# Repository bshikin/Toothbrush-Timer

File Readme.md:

Toothbrush Timer
=================

This is a repository for my toothbrush timer project. It contains schematic and enclosure design and program sources.

You can read how the timer was made in [this Instructable](http://instructables.com/id/Toothbrush-Timer)

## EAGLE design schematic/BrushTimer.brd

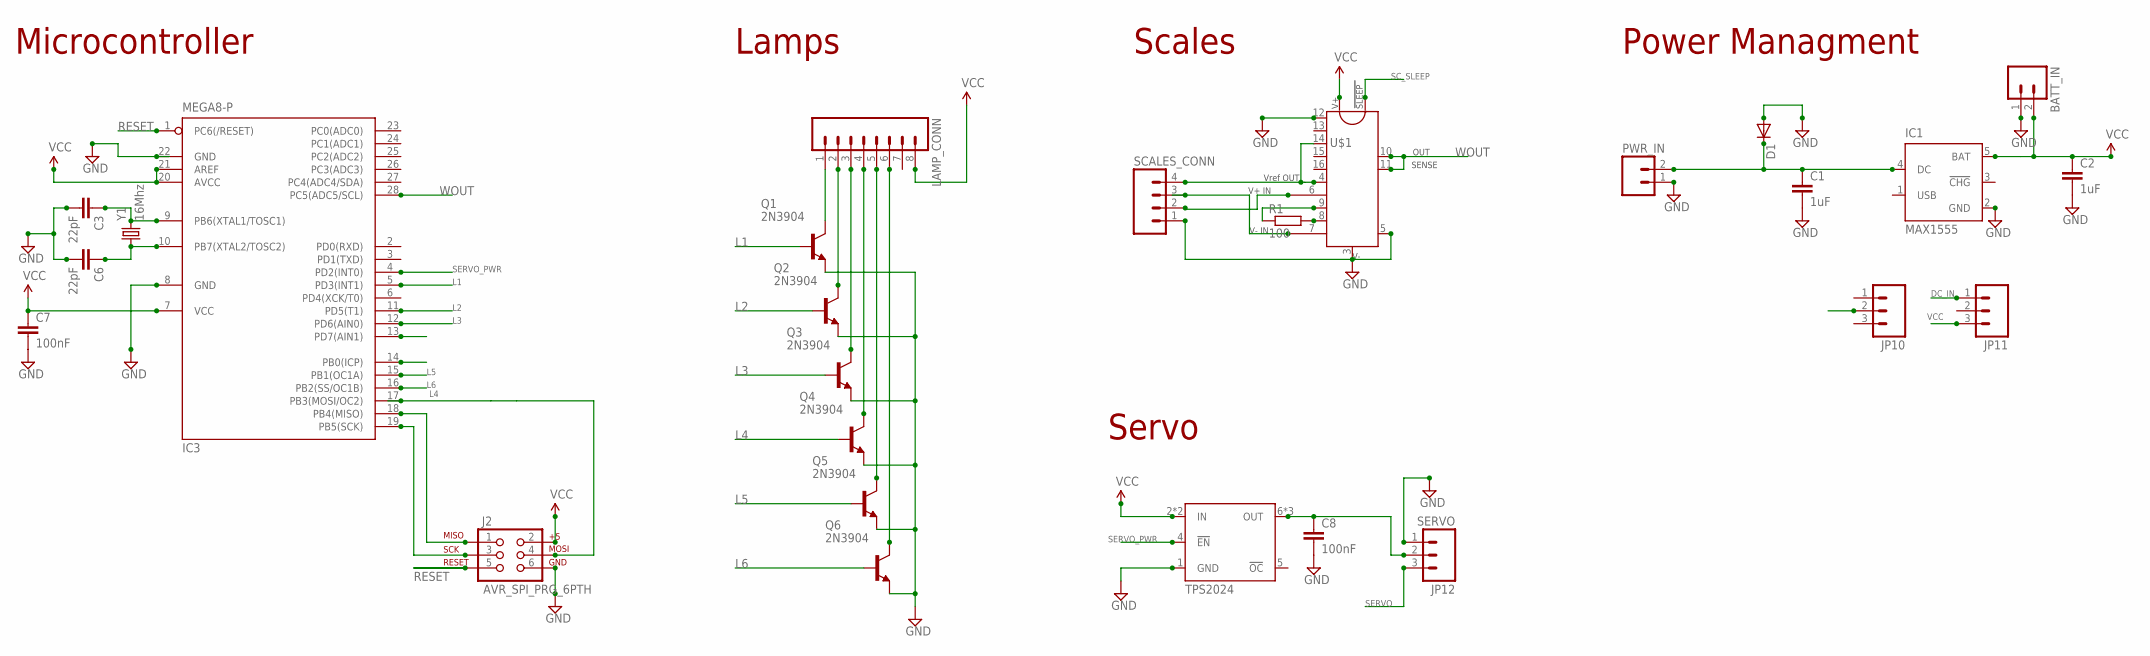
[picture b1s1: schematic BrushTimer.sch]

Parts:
BATT_IN: M02PTH; 1X02
C1, C2: 1uF; AXIAL-5MM
C3, C6: 22pF; C2.5-2
C7, C8: 100nF; C5B3.5
D1: DIODE-D-2.5; D-2.5
IC1: MAX1555; SOT23-5L
IC3: MEGA8-P; DIL28-3
J2: AVR_SPI_PRG_6PTH; 2X3
JP10, JP11: M03PTH; 1X03
JP12: SERVO; 1X03
LAMP_CONN: M081X08; 1X08
PWR_IN: M02PTH; 1X02
Q1, Q2, Q3, Q4, Q5, Q6: 2N3904; TO92
R1: 100; 0207/5V
SCALES_CONN: M04PTH; 1X04
U$1: INA125; DIL16
U$2: TPS2024; DIL08-OPTO
Y1: 16Mhz; HC49US

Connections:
DC_IN: C1.P$1 (1), D1.C, IC1.4 (DC), JP11.1, PWR_IN.2
GND: BATT_IN.1, C1.P$2 (2), C2.P$2 (2), C3.2, C6.2, C7.2, C8.2, D1.A, IC1.2 (GND), IC3.8 (GND), IC3.22 (GND), J2.6, JP10.2, JP12.1, PWR_IN.1, Q1.3 (E), Q2.3 (E), Q3.3 (E), Q4.3 (E), Q5.3 (E), Q6.3 (E), SCALES_CONN.1, U$1.3, U$1.5, U$1.12, U$2.1 (GND)
L1: IC3.5 (PD3(INT1)), Q1.2 (B)
L1_OUT: LAMP_CONN.1, Q1.1 (C)
L2: IC3.11 (PD5(T1)), Q2.2 (B)
L2_OUT: LAMP_CONN.2, Q2.1 (C)
L3: IC3.12 (PD6(AIN0)), Q3.2 (B)
L3_OUT: LAMP_CONN.3, Q3.1 (C)
L4: IC3.17 (PB3(MOSI/OC2)), J2.4, Q4.2 (B)
L4_OUT: LAMP_CONN.4, Q4.1 (C)
L5: IC3.15 (PB1(OC1A)), Q5.2 (B)
L5_OUT: LAMP_CONN.5, Q5.1 (C)
L6: IC3.16 (PB2(SS/OC1B)), Q6.2 (B)
L6_OUT: LAMP_CONN.6, Q6.1 (C)
MISO: IC3.18 (PB4(MISO)), J2.1
unnamed: SCALES_CONN.2, U$1.6
RESET: IC3.1 (PC6(/RESET)), J2.5
RG1: R1.1, U$1.9
RG2: R1.2, U$1.8
SCK: IC3.19 (PB5(SCK)), J2.3
SC_SLEEP: IC3.13 (PD7(AIN1)), U$1.2
SERVO: IC3.14 (PB0(ICP)), JP12.3
SERVO_PWR: IC3.4 (PD2(INT0)), U$2.4 (!EN)
SERVO_VCC: C8.1, JP12.2, U$2.6 (OUT), U$2.7 (OUT), U$2.8 (OUT)
V-IN: SCALES_CONN.3, U$1.7
VCC: BATT_IN.2, C2.P$1 (1), C7.1, IC1.5 (BAT), IC3.7 (VCC), IC3.20 (AVCC), IC3.21 (AREF), J2.2, JP11.3, LAMP_CONN.8, U$1.1, U$2.2 (IN), U$2.3 (IN)
VREF-OUT: SCALES_CONN.4, U$1.4, U$1.14
WOUT: IC3.28 (PC5(ADC5/SCL)), U$1.10, U$1.11
XTAL9: C3.1, IC3.9 (PB6(XTAL1/TOSC1)), Y1.2
XTAL19: C6.1, IC3.10 (PB7(XTAL2/TOSC2)), Y1.1

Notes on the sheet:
Microcontroller
Lamps
Scales
Power Managment
Servo

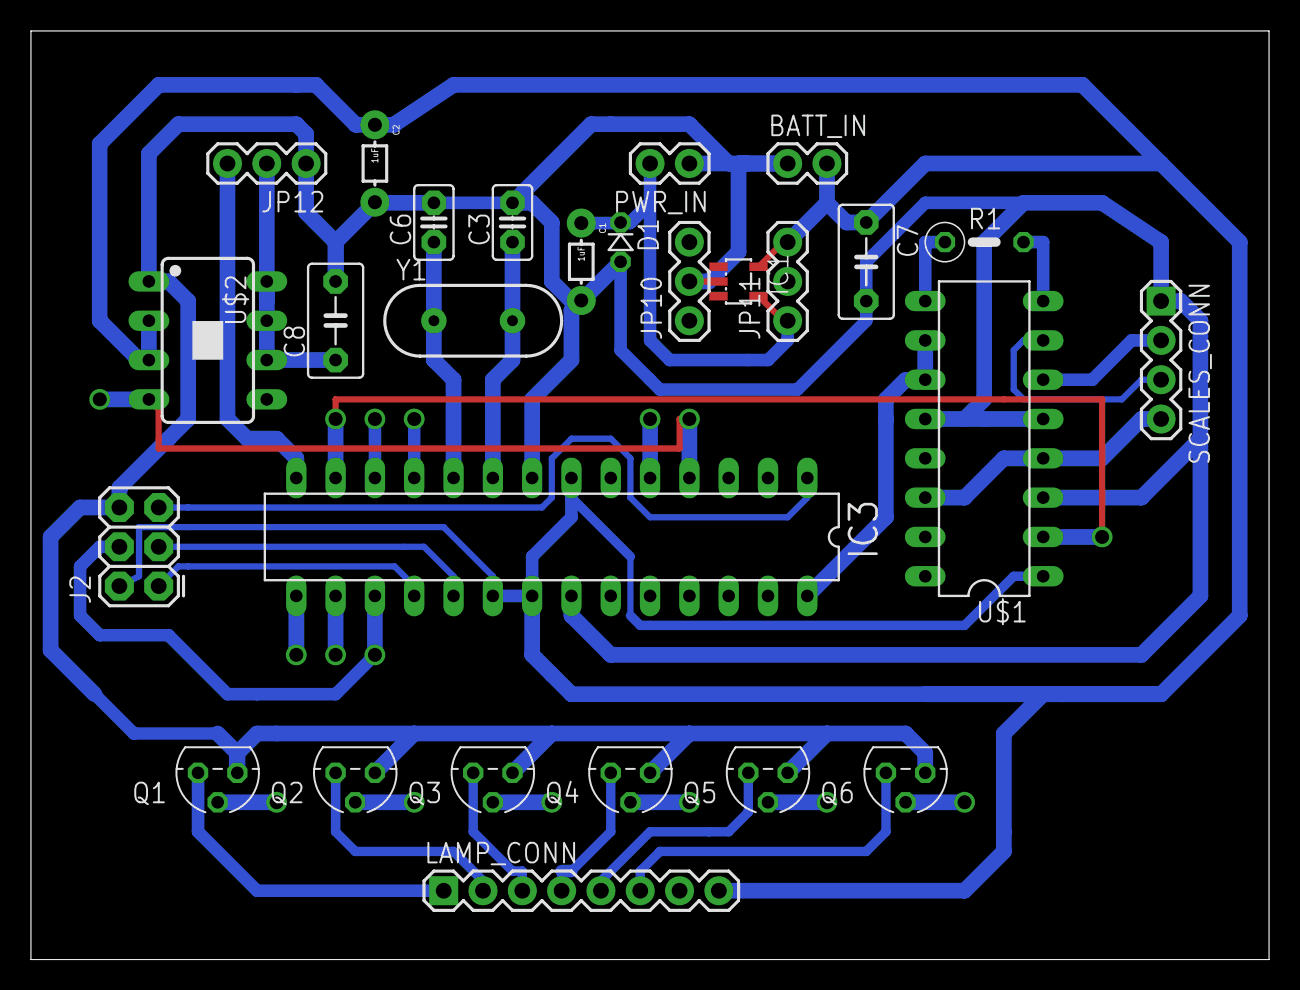
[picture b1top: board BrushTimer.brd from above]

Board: 2 copper layers, 80.0 x 60.0 mm, 27 parts (0 on the bottom side), 30 nets.

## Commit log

2012-07-04 Initial checkin
2012-07-04 Update master

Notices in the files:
parts and their libraries:
SparkFun: Licensing: CC v3.0 Share-Alike You are welcome to use this library for commercial purposes.
